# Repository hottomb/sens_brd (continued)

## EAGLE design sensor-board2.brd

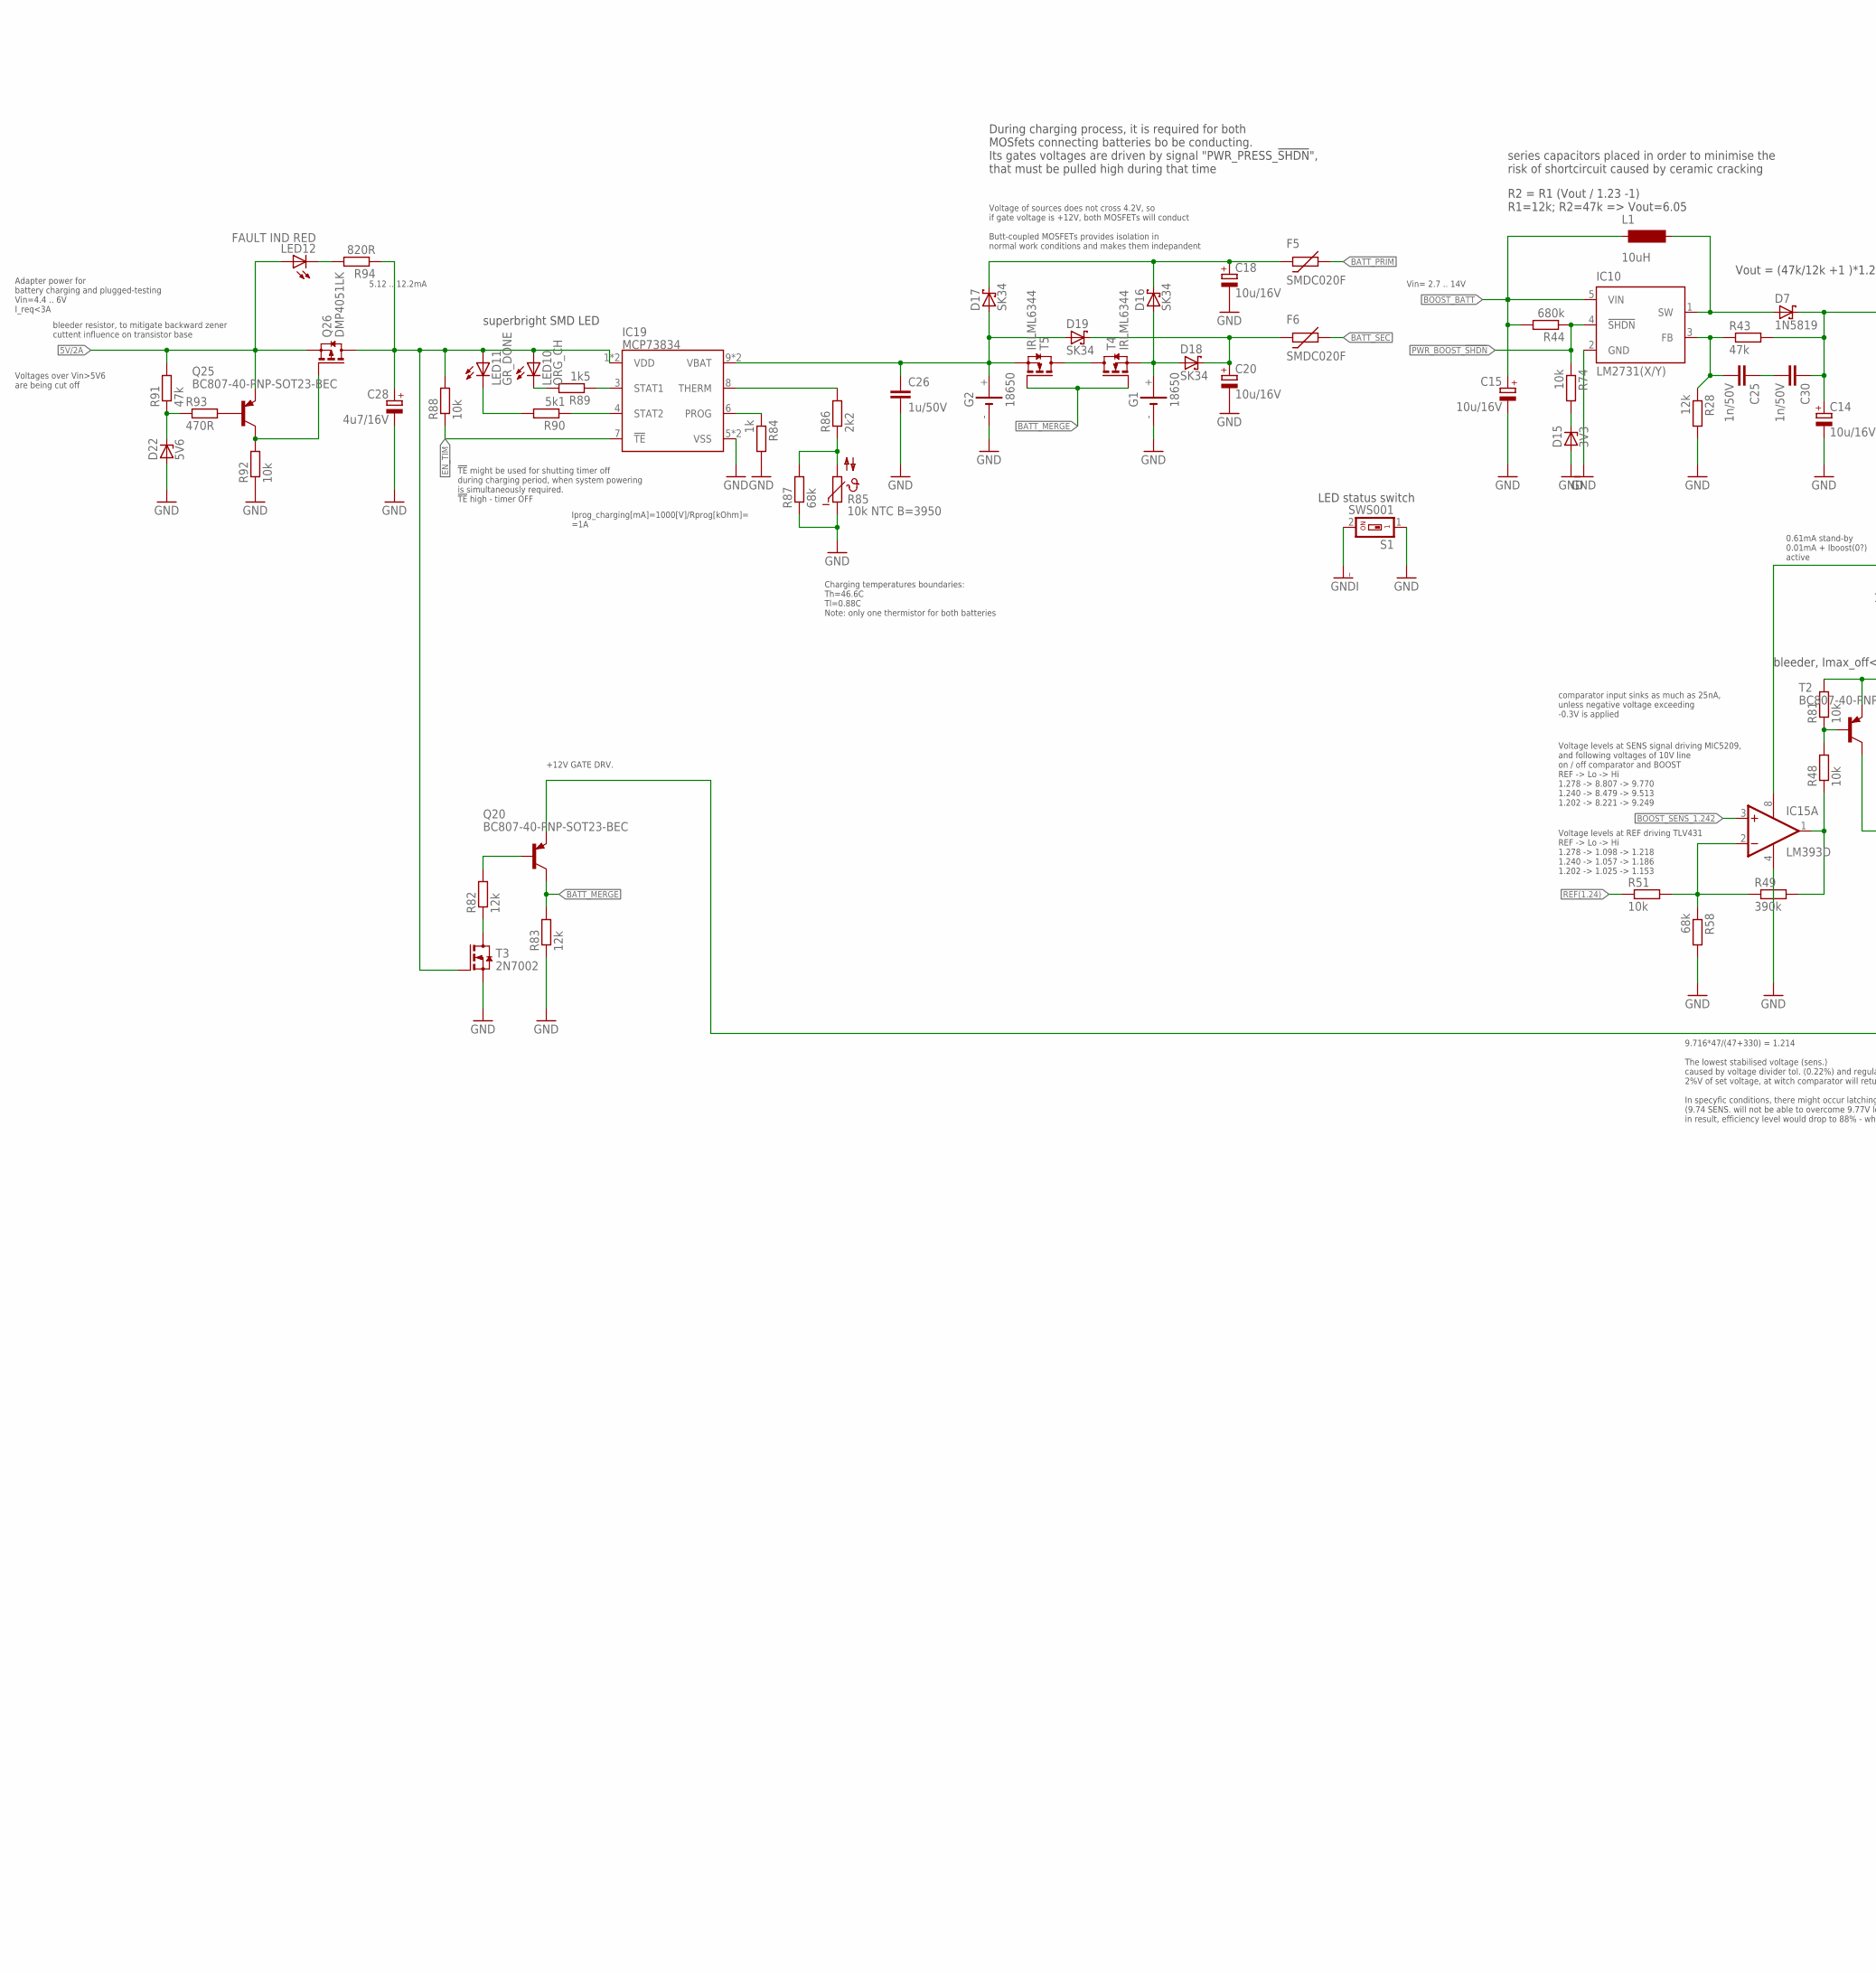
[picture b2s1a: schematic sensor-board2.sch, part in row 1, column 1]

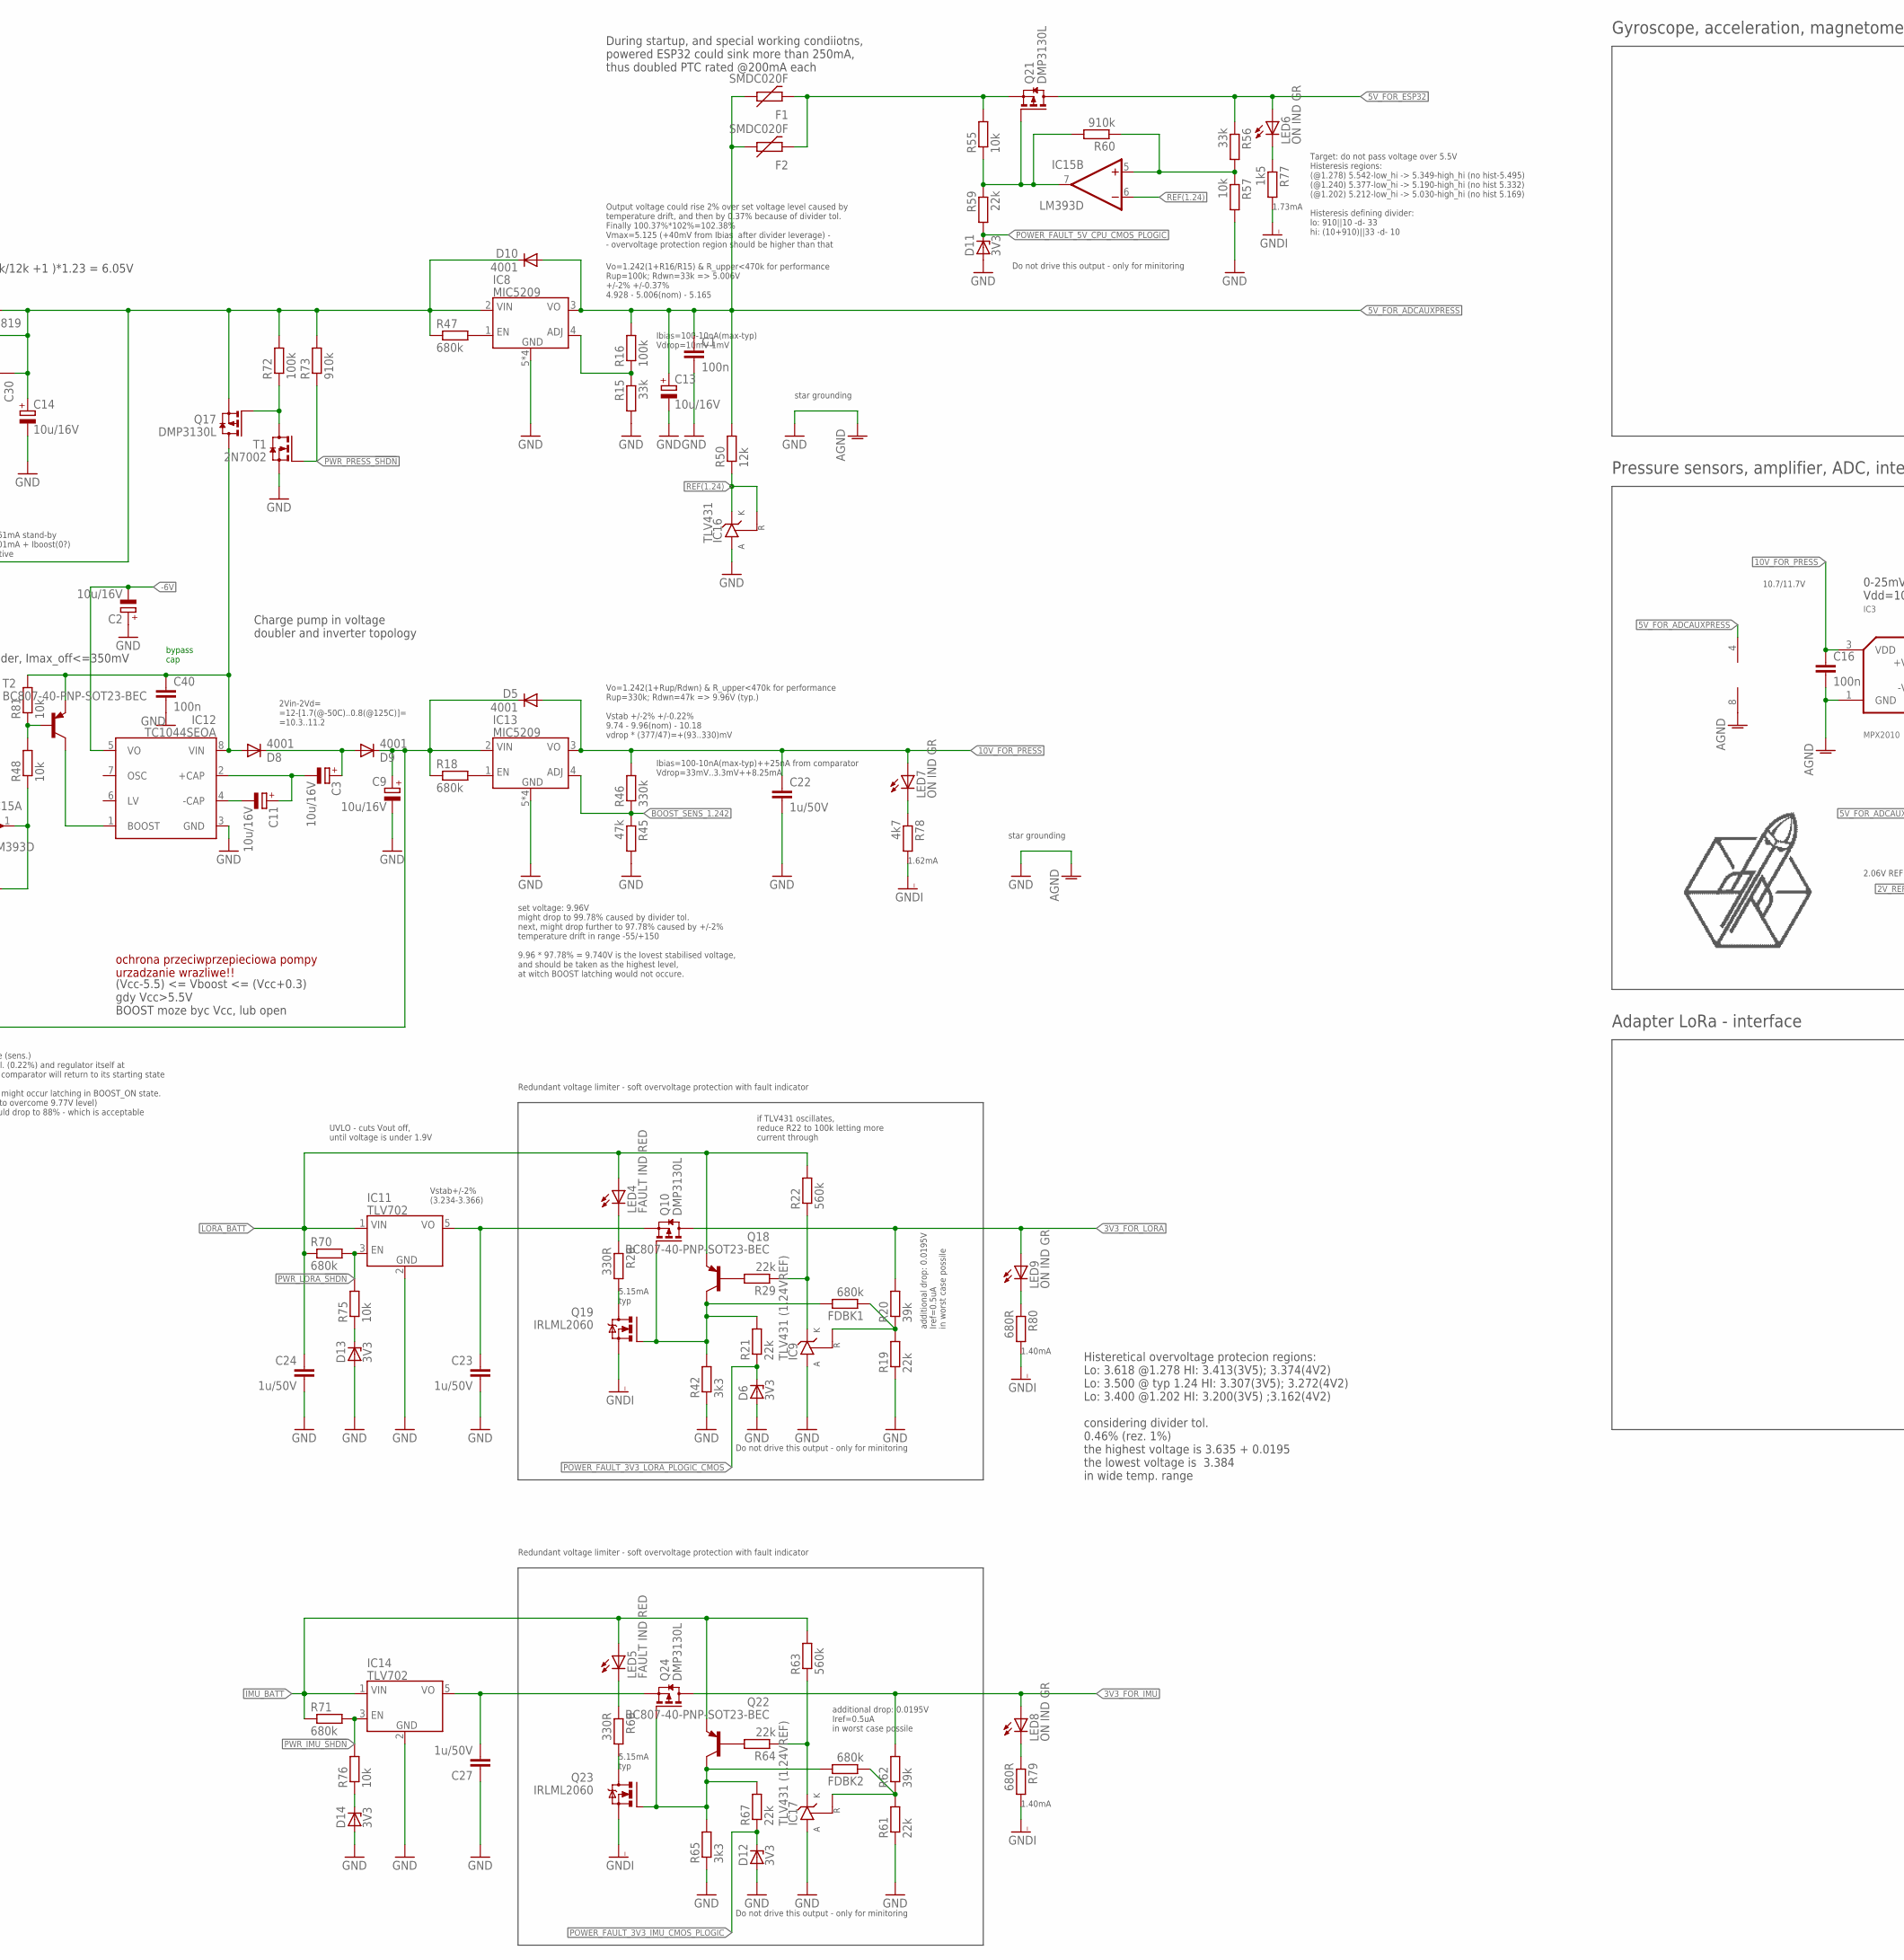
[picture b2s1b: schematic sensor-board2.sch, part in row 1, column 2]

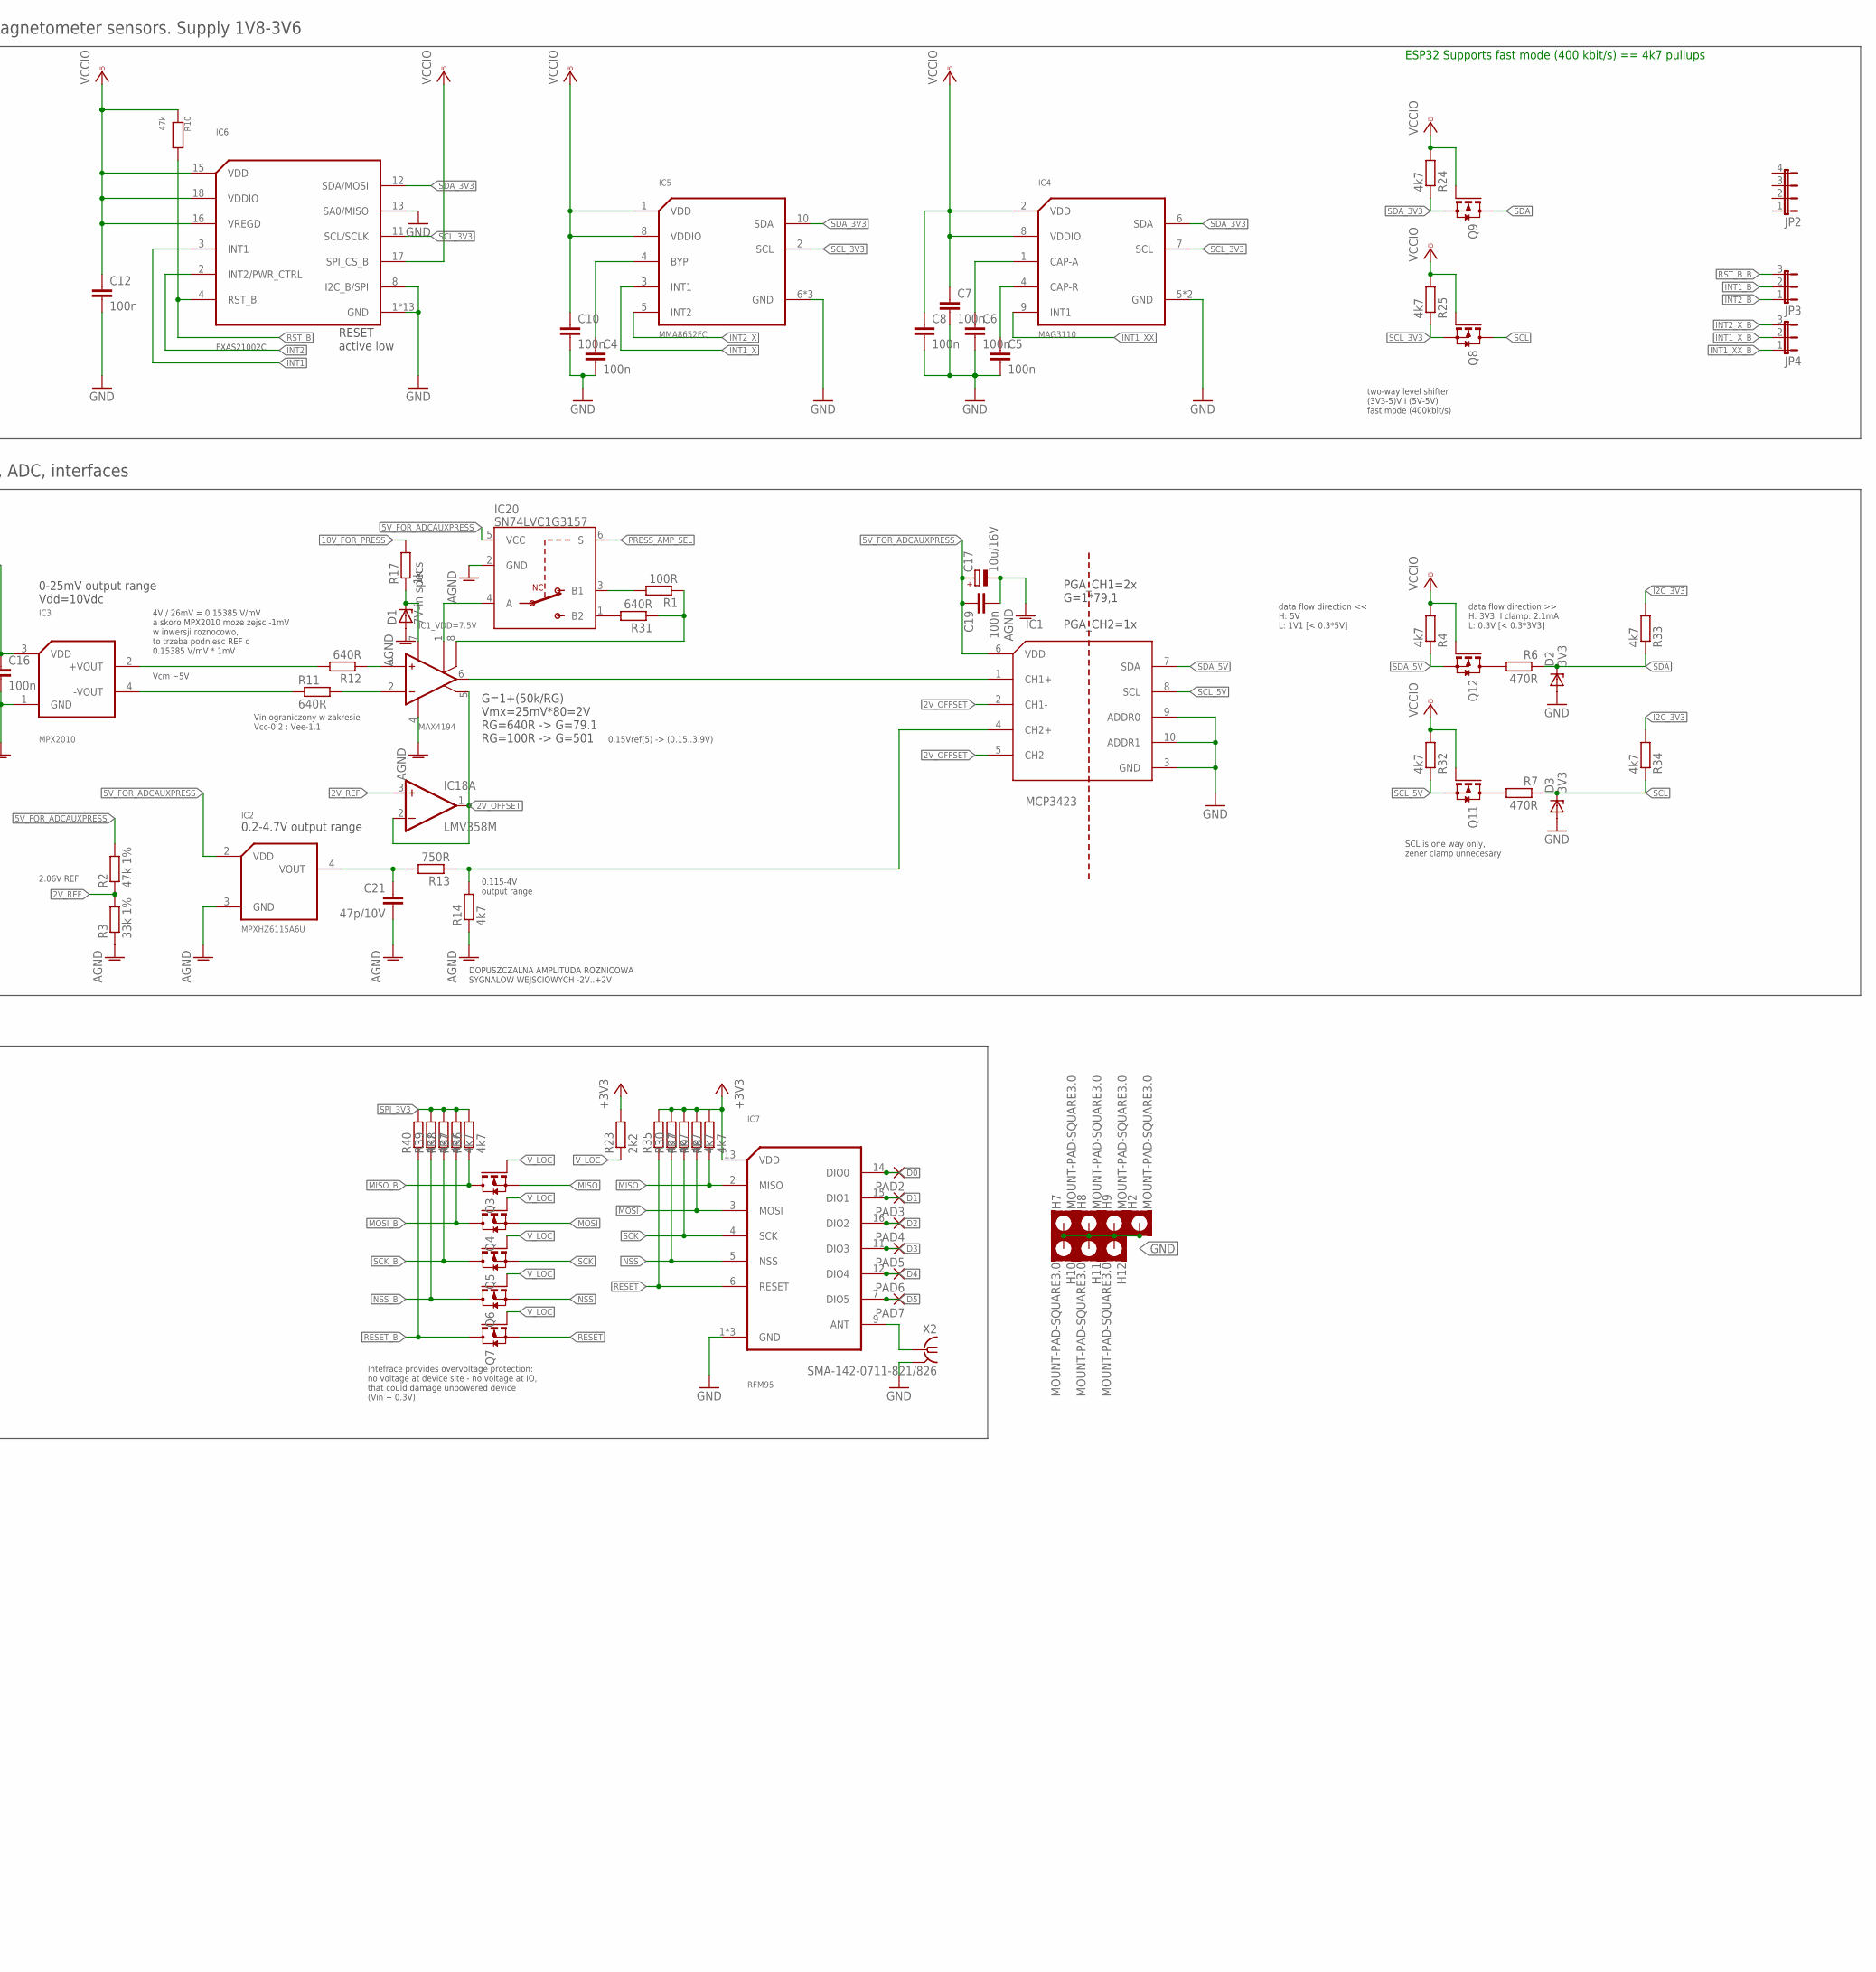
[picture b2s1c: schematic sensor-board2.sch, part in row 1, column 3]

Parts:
C1, C4, C5, C6, C7, C8, C10, C12, C16, C19, C40: 100n; C0805
C2, C3, C9, C11, C13, C14, C15, C17, C18, C20: 10u/16V; TANTAL"3216"
C21: 47p/10V; C0805
C22, C23, C24, C26, C27: 1u/50V; C1206
C25, C30: 1n/50V; C1206
C28: 4u7/16V; TANTAL"3216"
D1: 7V-in specs; SOD80C
D2, D3: 3V3; SOD323
D5, D8, D9, D10: 4001; DO-214AC
D6, D11, D12, D13, D14, D15: 3V3; SOD80C
D7: 1N5819; MELF-MLL41
D16, D17, D18, D19: SK34; SMA(DO214-AC)
D22: 5V6; SOD80C
F1, F2, F5, F6: SMDC020F; 1812
FDBK1, FDBK2: 680k; R0805
G1, G2: 18650; SL-150-1/2AA/PR
H2, H7, H8, H9, H10, H11, H12: MOUNT-PAD-SQUARE3.0; 3,0-PAD-SQUARE
IC1: MCP3423; MSOP10
IC1_VDD=7.5V: MAX4194; SO-8
IC2: MPXHZ6115A6U; SSOP_CASE_1317
IC3: MPX2010; SOP_CASE_482/A
IC4: MAG3110; 10_PIN_QFN_2X2MM
IC5: MMA8652FC; 10_PIN_QFN_2X2MM
IC6: FXAS21002C; 24_QFN_4X4MM
IC7: RFM95
IC8, IC13: MIC5209; SOIC8
IC9, IC17: TLV431 (1.24VREF); SOT23-3
IC10: LM2731(X/Y); SOT23-5
IC11, IC14: TLV702; SOT23-5
IC12: TC1044SEOA; SOIC8
IC15: LM393D; SO08
IC16: TLV431; SOT23-3
IC18: LMV358M; SO08
IC19: MCP73834; DFN10-3X3
IC20: SN74LVC1G3157; SC70-6
JP2: JP4E; JP4
JP3, JP4: JP2E; JP2
L1: 10uH; 7X7X4
LED4, LED5, LED12: FAULT IND RED; LED_1206
LED6, LED7, LED8, LED9: ON IND GR; LED_1206
LED10: ORG_CH; LED_1206
LED11: GR_DONE; LED_1206
PAD2, PAD3, PAD4, PAD5, PAD6, PAD7: SMD2; SMD1,27-2,54
Q3, Q4, Q5, Q6, Q7, Q8, Q9, Q11, Q12: AO3402; SOT23-3
Q10, Q17, Q21, Q24: DMP3130L; SOT23-3
Q18, Q20, Q22, Q25: BC807-40-PNP-SOT23-BEC; SOT23-BEC
Q19, Q23: IRLML2060; SOT23-3
Q26: DMP4051LK; TO252-3-11
R1: 100R; R0805
R2: 47k 1%; R0805
R3: 33k 1%; R0805
R4, R8, R9, R14, R24, R25, R27, R30, R32, R33, R34, R35, R36, R37, R38, R39, R40, R78: 4k7; R0805
R6, R7, R93: 470R; R0805
R10: 47k; ZWORA@1
R11, R12, R31: 640R; R0805
R13: 750R; R0805
R15, R56: 33k; R0805
R16, R72: 100k; R0805
R17, R84: 1k; R0805
R18, R44, R47, R70, R71: 680k; R0805
R19, R21, R29, R59, R61, R64, R67: 22k; R0805
R20, R62: 39k; R0805
R22, R63: 560k; R0805
R23, R86: 2k2; R0805
R26, R66: 330R; R0805
R28, R50, R82, R83: 12k; R0805
R42, R65: 3k3; R0805
R43, R45, R91: 47k; R0805
R46: 330k; R0805
R48, R51, R55, R57, R74, R75, R76, R81, R88, R92: 10k; R0805
R49: 390k; R0805
R58, R87: 68k; R0805
R60, R73: 910k; R0805
R77, R89: 1k5; R0805
R79, R80: 680R; R0805
R85: 10k NTC B=3950; N640
R90: 5k1; R0805
R94: 820R; R0805
S1: SWS001; SMS-001
T1, T3: 2N7002; SOT23-3W
T2: BC807-40-PNP-SOT23-BEC; SOT23-BEC
T4, T5: IRLML6344; SOT23-3W@1
X2: SMA-142-0711-821/826; J502-ND-142-0711-821/826

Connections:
2V_OFFSET: IC1.2 (CH1-), IC1.5 (CH2-), IC1_VDD=7.5V.5 (REF), IC18.1 (OUT), IC18.2 (-IN)
2V_REF: IC18.3 (+IN), R2.1, R3.2
3V3_FOR_IMU: LED8.A, Q24.3 (D), R62.2
3V3_FOR_LORA: LED9.A, Q10.3 (D), R20.2
5V/2A: LED12.A, Q25.E, Q26.2 (S), R91.2
5V_FOR_ADCAUXPRESS: C1.1, C13.+, C17.+, C19.1, D10.A, F1.P$2 (2), F2.P$2 (2), IC1.6 (VDD), IC2.2 (VDD), IC8.3 (VO), IC18.4 (V-), IC20.5 (VCC), R2.2, R16.2, R50.2
5V_FOR_ESP32: LED6.A, Q21.3 (D), R56.1
10V_FOR_PRESS: C16.1, C22.1, D5.A, IC3.3 (VDD), IC13.3 (VO), LED7.A, R17.2, R46.2
+3V3: IC7.13 (VDD), R23.2
-6V: C2.-, IC12.5 (VO)
AGND: C16.2, C17.-, C19.2, C21.2, D1.A, IC1_VDD=7.5V.4 (GND), IC2.3 (GND), IC3.1 (GND), IC18.8 (V+), IC20.2 (GND), R3.1, R14.1
BATT_MERGE: Q20.C, R83.2, T4.1 (G), T5.1 (G)
BATT_PRIM: F5.P$2 (2)
BATT_SEC: F6.P$2 (2)
BOOST_BATT: C15.+, IC10.5 (VIN), L1.1, R44.2
BOOST_SENS_1.242: IC13.4 (ADJ), IC15.3 (+IN), R45.1, R46.1
D0: IC7.14 (DIO0), PAD2.1
D1: IC7.15 (DIO1), PAD3.1
D2: IC7.16 (DIO2), PAD4.1
D3: IC7.11 (DIO3), PAD5.1
D4: IC7.12 (DIO4), PAD6.1
D5: IC7.7 (DIO5), PAD7.1
EN_TIM: IC19.7 (!TE!), R88.1
GND: C1.2, C2.+, C4.2, C5.2, C6.2, C7.2, C8.2, C9.-, C10.2, C12.2, C13.-, C14.-, C15.-, C18.-, C20.-, C22.2, C23.2, C24.2, C26.2, C27.1, C28.-, C40.2, D2.A, D3.A, D6.A, D11.A, D12.A, D13.A, D14.A, D15.A, D22.A, G1.-, G2.-, H2.B3,0, H7.B3,0, H8.B3,0, H9.B3,0, H10.B3,0, H11.B3,0, H12.B3,0, IC1.3 (GND), IC1.9 (ADDR0), IC1.10 (ADDR1), IC4.5 (GND), IC4.10 (GND), IC5.6 (GND), IC5.7 (GND), IC5.9 (GND), IC6.1 (GND), IC6.5 (GND), IC6.6 (GND), IC6.7 (GND), IC6.8 (I2C_B/SPI), IC6.9 (GND), IC6.10 (GND), IC6.13 (SA0/MISO), IC6.14 (GND), IC6.19 (GND), IC6.20 (GND), IC6.21 (GND), IC6.22 (GND), IC6.23 (GND), IC6.24 (GND), IC7.1 (GND), IC7.8 (GND), IC7.10 (GND), IC8.5 (GND), IC8.6 (GND), IC8.7 (GND), IC8.8 (GND), IC9.3 (A), IC10.2 (GND), IC11.2 (GND), IC12.3 (GND), IC13.5 (GND), IC13.6 (GND), IC13.7 (GND), IC13.8 (GND), IC14.2 (GND), IC15.4 (V-), IC16.3 (A), IC17.3 (A), IC19.5 (VSS), IC19.GND (VSS), R15.2, R19.1, R28.2, R42.1, R45.2, R57.2, R58.2, R61.1, R65.1, R83.1, R84.2, R85.1, R87.1, R92.1, S1.1, T1.2 (S), T3.2 (S), X2.G@1 (2), X2.G@2 (2), X2.G@3 (2), X2.G@4 (2)
GNDI: Q19.2 (S), Q23.2 (S), R77.2, R78.2, R79.2, R80.2, S1.2
I2C_3V3: R33.2, R34.2
IMU_BATT: IC14.1 (VIN), LED5.A, Q22.E, R63.2, R71.1
INT1: IC6.3 (INT1)
INT1_B: JP3.2
INT1_X: IC5.3 (INT1)
INT1_XX: IC4.9 (INT1)
INT1_XX_B: JP4.1
INT1_X_B: JP4.2
INT2: IC6.2 (INT2/PWR_CTRL)
INT2_B: JP3.1
INT2_X: IC5.5 (INT2)
INT2_X_B: JP4.3
LORA_BATT: C24.1, IC11.1 (VIN), LED4.A, Q18.E, R22.2, R70.1
MISO: IC7.2 (MISO), Q3.2 (S), R8.1
MISO_B: Q3.3 (D), R36.1
MOSI: IC7.3 (MOSI), Q4.2 (S), R9.1
MOSI_B: Q4.3 (D), R37.1
unnamed: IC1.1 (CH1+), IC1_VDD=7.5V.6 (VOUT)
unnamed: IC8.4 (ADJ), R15.1, R16.1
unnamed: Q12.3 (D), R6.2
unnamed: IC1_VDD=7.5V.2 (IN-), R11.2
unnamed: IC20.1 (B2), R31.2
unnamed: IC1_VDD=7.5V.1 (RG+), IC20.4 (A)
unnamed: IC3.4 (-VOUT), R11.1
unnamed: F1.P$1 (1), F2.P$1 (1), Q21.2 (S), R55.2
unnamed: C5.1, IC4.4 (CAP-R)
unnamed: C6.1, IC4.1 (CAP-A)
unnamed: C11.-, IC12.4 (-CAP)
unnamed: Q11.3 (D), R7.2
unnamed: R8.2, R9.2, R27.2, R30.2, R35.2
unnamed: IC7.9 (ANT), X2.1
unnamed: C21.1, IC2.4 (VOUT), R13.2
unnamed: C4.1, IC5.4 (BYP)
unnamed: C40.1, D8.A, IC12.8 (VIN), Q17.3 (D), R81.2, T2.E
unnamed: IC1.4 (CH2+), R13.1, R14.2
unnamed: IC8.1 (EN), R47.2
unnamed: IC1_VDD=7.5V.3 (IN+), R12.1
unnamed: IC15.7 (OUT), Q21.1 (G), R55.1, R59.1, R60.2
unnamed: C23.1, IC11.5 (VO), Q10.2 (S)
unnamed: R48.2, R81.1, T2.B
unnamed: IC20.3 (B1), R1.2
unnamed: IC3.2 (+VOUT), R12.2
unnamed: Q17.1 (G), R72.1, T1.3 (D)
unnamed: Q18.B, R29.2
unnamed: C3.+, D8.C, D9.A
unnamed: IC15.5 (+IN), R56.2, R57.1, R60.1
unnamed: D7.A, IC10.1 (SW), L1.2
unnamed: C25.2, IC10.3 (FB), R28.1, R43.1
unnamed: LED4.C, R26.1
unnamed: D1.C, IC1_VDD=7.5V.7 (VDD), R17.1
unnamed: IC9.2 (K), R22.1, R29.1
unnamed: IC1_VDD=7.5V.8 (RG-), R1.1, R31.1
unnamed: C3.-, C11.+, IC12.2 (+CAP)
unnamed: IC15.1 (OUT), R48.1, R49.2
unnamed: Q19.3 (D), R26.2
unnamed: C14.+, C30.1, D7.C, D10.C, IC8.2 (VIN), IC15.8 (V+), Q17.2 (S), R43.2, R47.1, R72.2, R73.2
unnamed: D15.C, R74.2
unnamed: IC15.2 (-IN), R49.1, R51.2, R58.1
unnamed: IC13.1 (EN), R18.2
unnamed: D13.C, R75.1
unnamed: FDBK1.1, IC9.1 (R), R19.2, R20.1
unnamed: Q22.B, R64.2
unnamed: IC17.2 (K), R63.1, R64.1
unnamed: LED5.C, R66.1
unnamed: Q23.3 (D), R66.2
unnamed: C27.2, IC14.5 (VO), Q24.2 (S)
unnamed: FDBK2.1, IC17.1 (R), R61.2, R62.1
unnamed: C26.1, D17.A, D19.A, G2.+, IC19.9 (VBAT), IC19.10 (VBAT), T5.2 (S)
unnamed: D14.C, R76.1
unnamed: C25.1, C30.2
unnamed: D16.A, D18.A, G1.+, T4.2 (S)
unnamed: C18.+, D16.C, D17.C, F5.P$1 (1)
unnamed: C20.+, D18.C, D19.C, F6.P$1 (1)
unnamed: C28.+, IC19.1 (VDD), IC19.2 (VDD), LED10.A, LED11.A, Q26.3 (D), R88.2, R94.1, T3.1 (G)
unnamed: LED6.C, R77.1
unnamed: LED7.C, R78.1
unnamed: LED8.C, R79.1
unnamed: LED9.C, R80.1
unnamed: T4.3 (D), T5.3 (D)
unnamed: IC12.1 (BOOST), T2.C
unnamed: R82.1, T3.3 (D)
unnamed: Q20.B, R82.2
unnamed: C9.+, D5.C, D9.C, IC13.2 (VIN), Q20.E, R18.1
unnamed: D22.C, R91.1, R93.1
unnamed: IC19.4 (STAT2), R90.1
unnamed: R85.2, R86.1, R87.2
unnamed: IC19.6 (PROG), R84.1
unnamed: IC19.8 (THERM), R86.2
unnamed: LED10.C, R89.2
unnamed: IC19.3 (STAT1), R89.1
unnamed: Q25.C, Q26.1 (G), R92.2
unnamed: LED11.C, R90.2
unnamed: Q25.B, R93.2
unnamed: LED12.C, R94.2
NSS: IC7.5 (NSS), Q6.2 (S), R30.1
NSS_B: Q6.3 (D), R39.1
POWER_FAULT_3V3_IMU_CMOS_PLOGIC: D12.C, R67.1
POWER_FAULT_3V3_LORA_PLOGIC_CMOS: D6.C, R21.1
POWER_FAULT_5V_CPU_CMOS_PLOGIC: D11.C, R59.2
PRESS_AMP_SEL: IC20.6 (S)
PWR_BOOST_!SHDN!: IC10.4 (!SHDN!), R44.1, R74.1
PWR_IMU_!SHDN!: IC14.3 (EN), R71.2, R76.2
PWR_LORA_!SHDN!: IC11.3 (EN), R70.2, R75.2
PWR_PRESS_!SHDN!: R73.1, T1.1 (G)
REF(1.24): IC15.6 (-IN), IC16.1 (R), IC16.2 (K), R50.1, R51.1
REHREH: FDBK1.2, Q10.1 (G), Q18.C, Q19.1 (G), R21.2, R42.2
REHREH1: FDBK2.2, Q22.C, Q23.1 (G), Q24.1 (G), R65.2, R67.2
RESET: IC7.6 (RESET), Q7.2 (S), R35.1
RESET_B: Q7.3 (D), R40.1
RST_B: IC6.4 (RST_B), R10.2
RST_B_B: JP3.3
SCK: IC7.4 (SCK), Q5.2 (S), R27.1
SCK_B: Q5.3 (D), R38.1
SCL: D3.C (K), Q8.3 (D), R7.1, R34.1
SCL_3V3: IC4.7 (SCL), IC5.2 (SCL), IC6.11 (SCL/SCLK), Q8.2 (S), R25.1
SCL_5V: IC1.8 (SCL), Q11.2 (S), R32.1
SDA: D2.C (K), Q9.3 (D), R6.1, R33.1
SDA_3V3: IC4.6 (SDA), IC5.10 (SDA), IC6.12 (SDA/MOSI), Q9.2 (S), R24.1
SDA_5V: IC1.7 (SDA), Q12.2 (S), R4.1
SPI_3V3: R36.2, R37.2, R38.2, R39.2, R40.2
VCCIO: C7.1, C8.1, C10.1, C12.1, IC4.2 (VDD), IC4.8 (VDDIO), IC5.1 (VDD), IC5.8 (VDDIO), IC6.15 (VDD), IC6.16 (VREGD), IC6.17 (SPI_CS_B), IC6.18 (VDDIO), Q8.1 (G), Q9.1 (G), Q11.1 (G), Q12.1 (G), R4.2, R10.1, R24.2, R25.2, R32.2
V_LOC: Q3.1 (G), Q4.1 (G), Q5.1 (G), Q6.1 (G), Q7.1 (G), R23.1

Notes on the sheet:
0-25mV output range Vdd=10Vdc
0.2-4.7V output range
G=1+(50k/RG) Vmx=25mV*80=2V RG=640R -> G=79.1 RG=100R -> G=501
PGA_CH1=2x G=1*79,1 PGA_CH2=1x
RESET active low
Pressure sensors, amplifier, ADC, interfaces
Gyroscope, acceleration, magnetometer sensors. Supply 1V8-3V6
10.7/11.7V
Adapter LoRa - interface
DOPUSZCZALNA AMPLITUDA ROZNICOWA SYGNALOW WEJSCIOWYCH -2V..+2V
0.115-4V output range
Histeretical overvoltage protecion regions: Lo: 3.618 @1.278 HI: 3.413(3V5); 3.374(4V2) Lo: 3.500 @ typ 1.24 HI: 3.307(3V5); 3.272(4V2) Lo: 3.400 @1.202 HI: 3.200(3V5) ;3.162(4V2) considering divider tol. 0.46% (rez. 1%) the highest voltage is 3.635 + 0.0195 the lowest voltage is 3.384 in wide temp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
Intefrace provides overvoltage protection: no voltage at device site - no voltage at IO, that could damage unpowered device (Vin + 0.3V)
Redundant voltage limiter - soft overvoltage protection with fault indicator
R2 = R1 (Vout / 1.23 -1) R1=12k; R2=47k => Vout=6.05
Vin ograniczony w zakresie Vcc-0.2 : Vee-1.1
2Vin-2Vd= =12-[1.7(@-50C)..0.8(@125C)]= =10.3..11.2
Vo=1.242(1+Rup/Rdwn) & R_upper<470k for performance Rup=330k; Rdwn=47k => 9.96V (typ.)
Vo=1.242(1+R16/R15) & R_upper<470k for performance Rup=100k; Rdwn=33k => 5.006V +/-2% +/-0.37% 4.928 - 5.006(nom) - 5.165
additional drop: 0.0195V Iref=0.5uA in worst case possile
Ibias=100-10nA(max-typ)++25nA from comparator Vdrop=33mV..3.3mV++8.25mA
Vstab+/-2% (3.234-3.366)
Vstab +/-2% +/-0.22% 9.74 - 9.96(nom) - 10.18 vdrop * (377/47)=+(93..330)mV
if TLV431 oscillates, reduce R22 to 100k letting more current through
9.716*47/(47+330) = 1.214 The lowest stabilised voltage (sens.) caused by voltage divider tol. (0.22%) and regulator itself at 2%V of set voltage, at witch comparator will return to its starting state In specyfic conditions, there might occur latching in BOOST_ON state. (9.74 SENS. will not be able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
comparator input sinks as much as 25nA, unless negative voltage exceeding -0.3V is applied
set voltage: 9.96V might drop to 99.78% caused by divider tol. next, might drop further to 97.78% caused by +/-2% temperature drift in range -55/+150 9.96 * 97.78% = 9.740V is the lovest stabilised voltage, and should be taken as the highest level, at witch BOOST latching would not occure.
Voltage levels at REF driving TLV431 REF -> Lo -> Hi 1.278 -> 1.098 -> 1.218 1.240 -> 1.057 -> 1.186 1.202 -> 1.025 -> 1.153
Voltage levels at SENS signal driving MIC5209, and following voltages of 10V line on / off comparator and BOOST REF -> Lo -> Hi 1.278 -> 8.807 -> 9.770 1.240 -> 8.479 -> 9.513 1.202 -> 8.221 -> 9.249
0.61mA stand-by 0.01mA + Iboost(0?) active
Output voltage could rise 2% over set voltage level caused by temperature drift, and then by 0.37% because of divider tol. Finally 100.37%*102%=102.38% Vmax=5.125 (+40mV from Ibias after divider leverage) - - overvoltage protection region should be higher than that
Ibias=100-10nA(max-typ) Vdrop=10mV-1mV
Target: do not pass voltage over 5.5V Histeresis regions: (@1.278) 5.542-low_hi -> 5.349-high_hi (no hist-5.495) (@1.240) 5.377-low_hi -> 5.190-high_hi (no hist 5.332) (@1.202) 5.212-low_hi -> 5.030-high_hi (no hist 5.169) Histeresis defining divider: lo: 910||10 -d- 33 hi: (10+910)||33 -d- 10
UVLO - cuts Vout off, until voltage is under 1.9V
Do not drive this output - only for minitoring
LED status switch
(Vcc-5.5) <= Vboost <= (Vcc+0.3) gdy Vcc>5.5V BOOST moze byc Vcc, lub open
bleeder, Imax_off<=350mV
Vout = (47k/12k +1 )*1.23 = 6.05V
+12V GATE DRV.

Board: 2 copper layers, 218 parts (0 on the bottom side), 133 nets, no tracks yet.

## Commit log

2017-10-24 adding blocks
2017-10-24 power supply improvement
2017-10-28 IO discrete buffers
2017-10-29 overvoltage protection
2017-10-30 overvoltage protection fix
2017-11-01 12/6/5 voltages added
2017-11-03 12-10 care with the BOOST mode
2017-11-05 All voltages protected
2017-11-24 Project leakage revoked
    All retards cured witch charger schem.
2017-11-24 file cleaning
2018-08-27 comments
2018-08-28 documentation update
